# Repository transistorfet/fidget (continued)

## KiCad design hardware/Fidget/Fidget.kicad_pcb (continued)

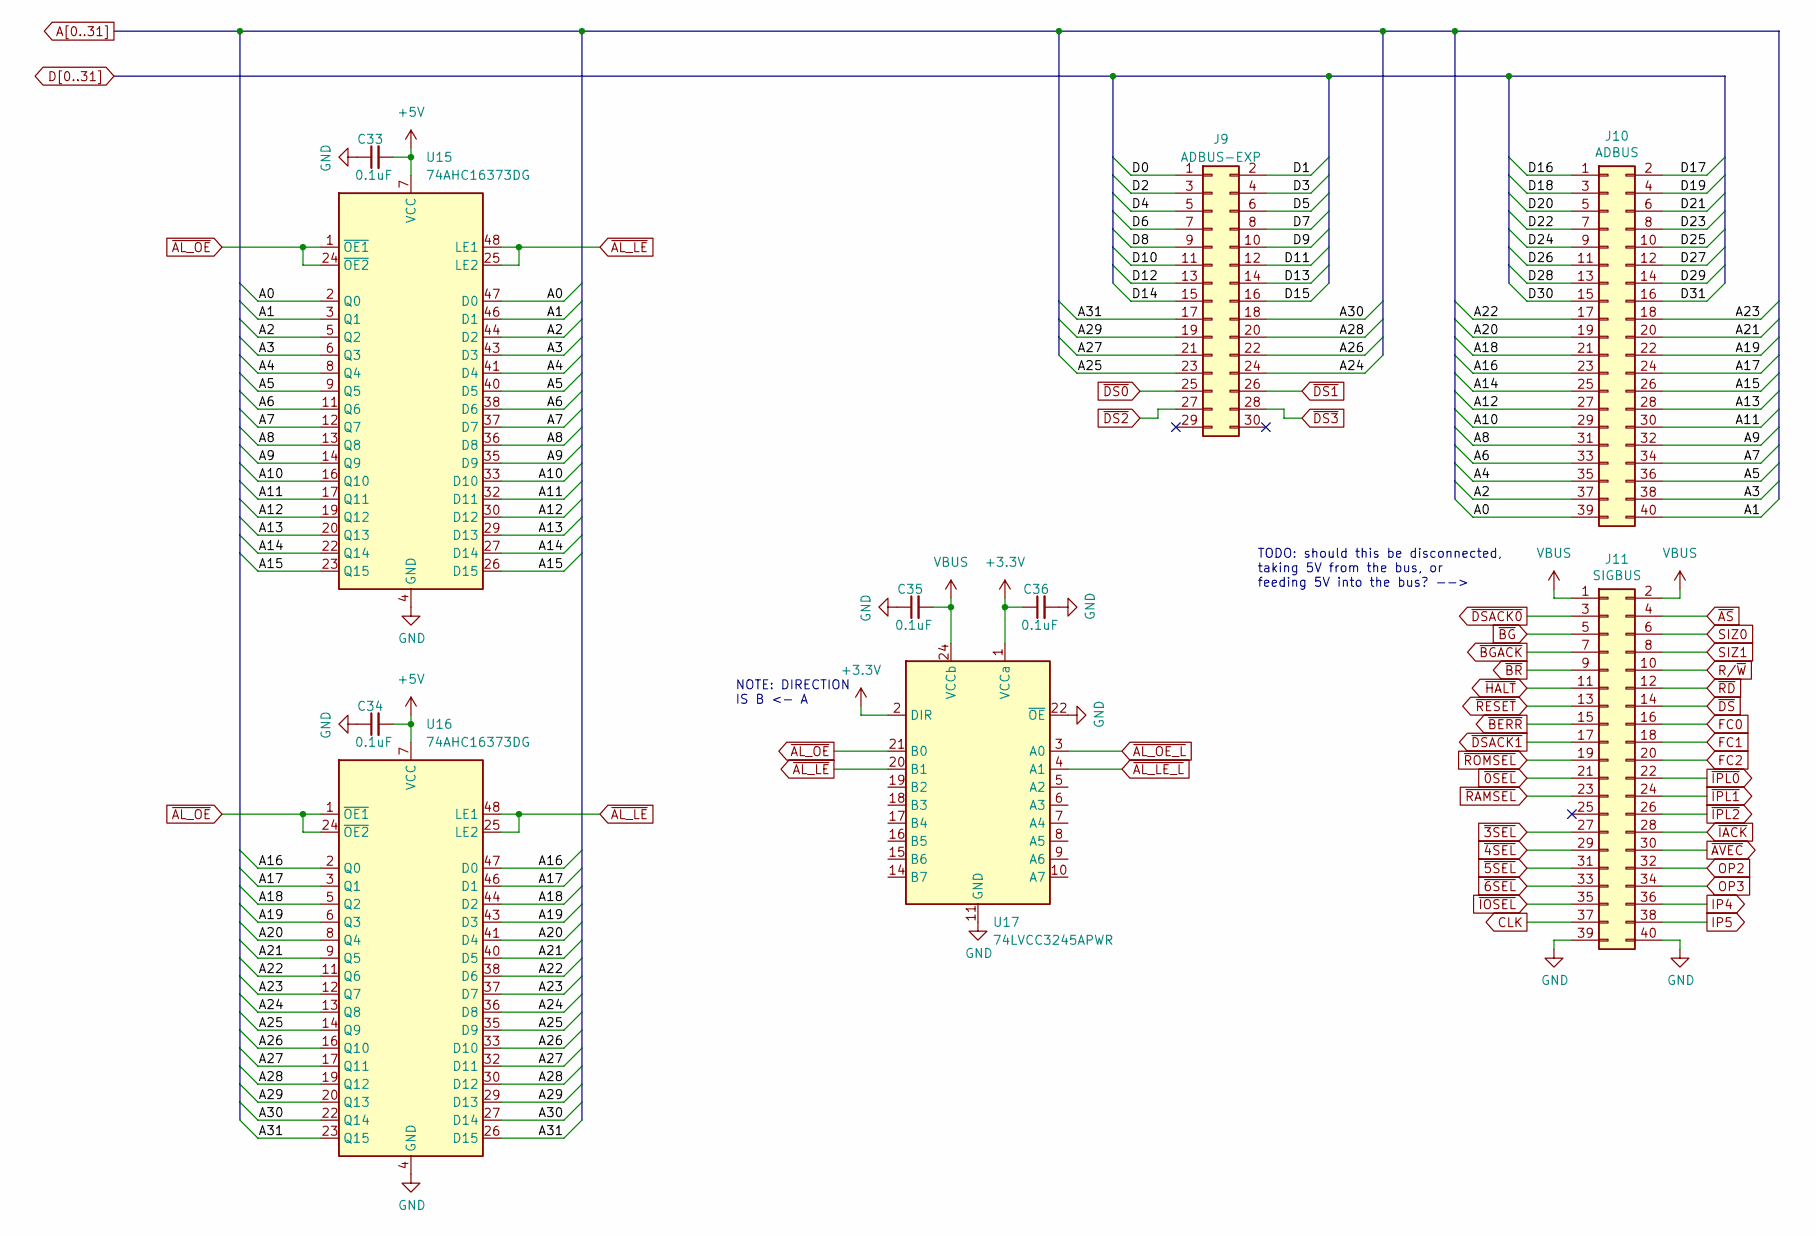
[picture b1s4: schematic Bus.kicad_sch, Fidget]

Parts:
C33, C34, C35, C36: 0.1uF; C_0805_2012Metric_Pad1.18x1.45mm_HandSolder
J9: ADBUS-EXP; PinHeader_2x15_P2.54mm_Vertical
J10: ADBUS; PinHeader_2x20_P2.54mm_Vertical
J11: SIGBUS; PinHeader_2x20_P2.54mm_Vertical
U15, U16: 74AHC16373DG; TSSOP-48_6.1x12.5mm_P0.5mm
U17: 74LVCC3245APWR; TSSOP-24_4.4x7.8mm_P0.65mm

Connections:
+3.3V: C36.1, U17.1 (VCCa), U17.2 (DIR); also elsewhere on the board
+5V: C33.2, C34.2, U15.7 (VCC), U15.18 (VCC), U15.31 (VCC), U15.42 (VCC), U16.7 (VCC), U16.18 (VCC), U16.31 (VCC), U16.42 (VCC); also elsewhere on the board
A0: J10.39, U15.2 (Q0), U15.47 (D0); also elsewhere on the board
A1: J10.40, U15.3 (Q1), U15.46 (D1); also elsewhere on the board
A2: J10.37, U15.5 (Q2), U15.44 (D2); also elsewhere on the board
A3: J10.38, U15.6 (Q3), U15.43 (D3); also elsewhere on the board
A4: J10.35, U15.8 (Q4), U15.41 (D4); also elsewhere on the board
A5: J10.36, U15.9 (Q5), U15.40 (D5); also elsewhere on the board
A6: J10.33, U15.11 (Q6), U15.38 (D6); also elsewhere on the board
A7: J10.34, U15.12 (Q7), U15.37 (D7); also elsewhere on the board
A8: J10.31, U15.13 (Q8), U15.36 (D8); also elsewhere on the board
A9: J10.32, U15.14 (Q9), U15.35 (D9); also elsewhere on the board
A10: J10.29, U15.16 (Q10), U15.33 (D10); also elsewhere on the board
A11: J10.30, U15.17 (Q11), U15.32 (D11); also elsewhere on the board
A12: J10.27, U15.19 (Q12), U15.30 (D12); also elsewhere on the board
A13: J10.28, U15.20 (Q13), U15.29 (D13); also elsewhere on the board
A14: J10.25, U15.22 (Q14), U15.27 (D14); also elsewhere on the board
A15: J10.26, U15.23 (Q15), U15.26 (D15); also elsewhere on the board
A16: J10.23, U16.2 (Q0), U16.47 (D0); also elsewhere on the board
A17: J10.24, U16.3 (Q1), U16.46 (D1); also elsewhere on the board
A18: J10.21, U16.5 (Q2), U16.44 (D2); also elsewhere on the board
A19: J10.22, U16.6 (Q3), U16.43 (D3); also elsewhere on the board
A20: J10.19, U16.8 (Q4), U16.41 (D4); also elsewhere on the board
A21: J10.20, U16.9 (Q5), U16.40 (D5); also elsewhere on the board
A22: J10.17, U16.11 (Q6), U16.38 (D6); also elsewhere on the board
A23: J10.18, U16.12 (Q7), U16.37 (D7); also elsewhere on the board
A24: J9.24, U16.13 (Q8), U16.36 (D8); also elsewhere on the board
A25: J9.23, U16.14 (Q9), U16.35 (D9); also elsewhere on the board
A26: J9.22, U16.16 (Q10), U16.33 (D10); also elsewhere on the board
A27: J9.21, U16.17 (Q11), U16.32 (D11); also elsewhere on the board
A28: J9.20, U16.19 (Q12), U16.30 (D12); also elsewhere on the board
A29: J9.19, U16.20 (Q13), U16.29 (D13); also elsewhere on the board
A30: J9.18, U16.22 (Q14), U16.27 (D14); also elsewhere on the board
A31: J9.17, U16.23 (Q15), U16.26 (D15); also elsewhere on the board
CLK: J11.37; also elsewhere on the board
D0: J9.1; also elsewhere on the board
D1: J9.2; also elsewhere on the board
D2: J9.3; also elsewhere on the board
D3: J9.4; also elsewhere on the board
D4: J9.5; also elsewhere on the board
D5: J9.6; also elsewhere on the board
D6: J9.7; also elsewhere on the board
D7: J9.8; also elsewhere on the board
D8: J9.9; also elsewhere on the board
D9: J9.10; also elsewhere on the board
D10: J9.11; also elsewhere on the board
D11: J9.12; also elsewhere on the board
D12: J9.13; also elsewhere on the board
D13: J9.14; also elsewhere on the board
D14: J9.15; also elsewhere on the board
D15: J9.16; also elsewhere on the board
D16: J10.1; also elsewhere on the board
D17: J10.2; also elsewhere on the board
D18: J10.3; also elsewhere on the board
D19: J10.4; also elsewhere on the board
D20: J10.5; also elsewhere on the board
D21: J10.6; also elsewhere on the board
D22: J10.7; also elsewhere on the board
D23: J10.8; also elsewhere on the board
D24: J10.9; also elsewhere on the board
D25: J10.10; also elsewhere on the board
D26: J10.11; also elsewhere on the board
D27: J10.12; also elsewhere on the board
D28: J10.13; also elsewhere on the board
D29: J10.14; also elsewhere on the board
D30: J10.15; also elsewhere on the board
D31: J10.16; also elsewhere on the board
FC0: J11.16; also elsewhere on the board
FC1: J11.18; also elsewhere on the board
FC2: J11.20; also elsewhere on the board
GND: C33.1, C34.1, C35.1, C36.2, J11.39, J11.40, U15.4 (GND), U15.10 (GND), U15.15 (GND), U15.21 (GND), U15.28 (GND), U15.34 (GND), U15.39 (GND), U15.45 (GND), U16.4 (GND), U16.10 (GND), U16.15 (GND), U16.21 (GND), U16.28 (GND), U16.34 (GND), U16.39 (GND), U16.45 (GND), U17.11 (GND), U17.12 (GND), U17.13 (GND), U17.22 (~OE); also elsewhere on the board
IP4: J11.36
IP5: J11.38
OP2: J11.32
OP3: J11.34
R/~W: J11.10; also elsewhere on the board
SIZ0: J11.6; also elsewhere on the board
SIZ1: J11.8; also elsewhere on the board
VBUS: C35.2, J11.1, J11.2, U17.24 (VCCb); also elsewhere on the board
~0SEL: J11.21
~3SEL: J11.27
~4SEL: J11.29
~5SEL: J11.31
~6SEL: J11.33
~AL_LE_L: U17.4 (A1); also elsewhere on the board
~AL_LE: U15.25 (LE2), U15.48 (LE1), U16.25 (LE2), U16.48 (LE1), U17.20 (B1)
~AL_OE_L: U17.3 (A0); also elsewhere on the board
~AL_OE: U15.1 (~OE1), U15.24 (~OE2), U16.1 (~OE1), U16.24 (~OE2), U17.21 (B0)
~AS: J11.4; also elsewhere on the board
~AVEC: J11.30; also elsewhere on the board
~BERR: J11.15; also elsewhere on the board
~BGACK: J11.7; also elsewhere on the board
~BG: J11.5; also elsewhere on the board
~BR: J11.9; also elsewhere on the board
~DS0: J9.25
~DS1: J9.26
~DS2: J9.27
~DS3: J9.28
~DSACK0: J11.3; also elsewhere on the board
~DSACK1: J11.17; also elsewhere on the board
~DS: J11.14; also elsewhere on the board
~HALT: J11.11; also elsewhere on the board
~IACK: J11.28; also elsewhere on the board
~IOSEL: J11.35
~IPL0: J11.22; also elsewhere on the board
~IPL1: J11.24; also elsewhere on the board
~IPL2: J11.26; also elsewhere on the board
~RAMSEL: J11.23
~RD: J11.12
~RESET: J11.13; also elsewhere on the board
~ROMSEL: J11.19

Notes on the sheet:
NOTE: DIRECTION IS B <- A
TODO: should this be disconnected, taking 5V from the bus, or feeding 5V into the bus? -->

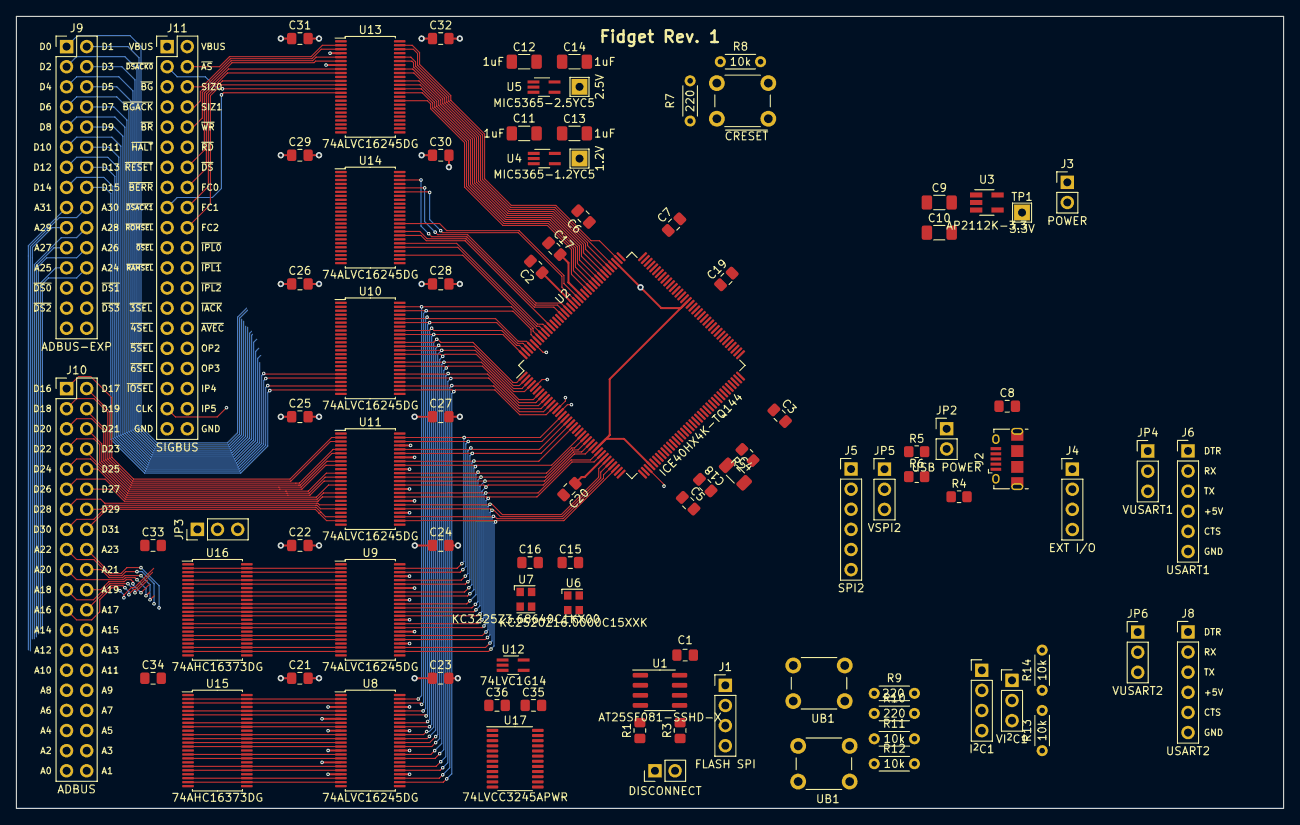
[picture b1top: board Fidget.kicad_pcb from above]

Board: 4 copper layers, 160.0 x 100.0 mm, 91 parts (0 on the bottom side), 204 nets.

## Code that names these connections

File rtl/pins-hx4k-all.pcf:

#
# FPGA:		Lattice iCE40 HX4K
# Package:	TQ-144
#
set_io -nowarn pin_ad[6]		1	# IOL_2A
set_io -nowarn pin_ad[7]		2       # IOL_2B
set_io -nowarn pin_ad[8]		3       # IOL_3A
set_io -nowarn pin_ad[9]		4       # IOL_3B
set_io -nowarn pin_ad[10]		7       # IOL_4A
set_io -nowarn pin_ad[11]		8       # IOL_4B
set_io -nowarn pin_ad[12]		9       # IOL_5A
set_io -nowarn pin_ad[13]		10      # IOL_5B
set_io -nowarn pin_ad[14]		11      # IOL_8A
set_io -nowarn pin_ad[15]		12      # IOL_8B
set_io -nowarn pin_ad[16]		15      # IOL_10A
set_io -nowarn pin_ad[17]		16      # IOL_10B
set_io -nowarn pin_ad[18]		17      # IOL_12A
set_io -nowarn pin_ad[19]		18      # IOL_12B
set_io -nowarn pin_ad[20]		19      # IOL_13A
set_io -nowarn pin_halt_in		20      # IOL_13B_GBIN7
set_io -nowarn pin_iack			21      # IOL_14A_GBIN6
set_io -nowarn pin_ad[21]		22      # IOL_14B
set_io -nowarn pin_ad[22]      		23      # IOL_17A
set_io -nowarn pin_ad[23]      		24      # IOL_17B
set_io -nowarn pin_ad[24]		25      # IOL_18A
set_io -nowarn pin_ad[25]		26      # IOL_18B
set_io -nowarn pin_ad[26]		28      # IOL_23A
set_io -nowarn pin_ad[27]		29      # IOL_23B
set_io -nowarn pin_ad[28]      		31      # IOL_24A
set_io -nowarn pin_ad[29]      		32      # IOL_24B
set_io -nowarn pin_ad[30]		33      # IOL_25A
set_io -nowarn pin_ad[31]		34      # IOL_25B
set_io -nowarn pin_avec			37      # IOB_56
set_io -nowarn pin_ctrl_oe     		38      # IOB_57
set_io -nowarn pin_alt_ctrl_oe 		39      # IOB_61
set_io -nowarn pin_alt_ctrl_dir1	41      # IOB_63
set_io -nowarn pin_alt_ctrl_dir2	42      # IOB_64
set_io -nowarn pin_data_dir		43      # IOB_71
set_io -nowarn pin_data_oe		44      # IOB_72
set_io -nowarn pin_send_receive		45      # IOB_73
set_io -nowarn pin_clk_16M		47      # IOB_79
set_io -nowarn pin_clk_3_6864M		48      # IOB_80
set_io -nowarn pin_addr_oe		49      # IOB_81_GBIN5
set_io -nowarn pin_al_oe		52      # IOB_82_GBIN4
set_io -nowarn pin_al_le		55      # IOB_91
set_io -nowarn pin_ul1			56      # IOB_94
set_io -nowarn pin_ul2			60      # IOB_95
set_io -nowarn pin_ul3			61      # IOB_96
set_io -nowarn pin_ul4			62      # IOB_102
set_io -nowarn pin_ub1			63      # IOB_103_CBSEL0
set_io -nowarn pin_ub2			64      # IOB_104_CBSEL1
set_io -nowarn pin_sdo			67      # IOB_105_SDO
set_io -nowarn pin_sdi			68      # IOB_106_SDI
set_io -nowarn pin_sck			70      # IOB_107_SCK
set_io -nowarn pin_scs			71      # IOB_108_SS
set_io -nowarn pin_sf_wp		73      # IOR_109
set_io -nowarn pin_sf_hold		74      # IOR_110
set_io -nowarn pin_sdo2			75      # IOR_111
set_io -nowarn pin_sdi2			76      # IOR_112
set_io -nowarn pin_sck2			78      # IOR_114
set_io -nowarn pin_scs2			79      # IOR_115
set_io -nowarn pin_sck1			80      # IOR_116
set_io -nowarn pin_sda1			81      # IOR_117
set_io -nowarn pin_usb_dn		82      # IOR_118
set_io -nowarn pin_usb_dp		83      # IOR_119
set_io -nowarn pin_usb_pullup		84      # IOR_120
set_io -nowarn pin_usart1_tx		85      # IOR_128
set_io -nowarn pin_usart1_rx		87      # IOR_136
set_io -nowarn pin_usart1_cts		88      # IOR_137, DTR on Rev1 (Input into FPGA)
set_io -nowarn pin_usart1_rts		90      # IOR_138, CTS on Rev1 (Output from FPGA)
set_io -nowarn pin_usart2_tx		91      # IOR_139
set_io -nowarn pin_usart2_rx		93      # IOR_140_GBIN3
set_io -nowarn pin_usart2_cts		94      # IOR_141_GBIN2, DTR on Rev1 (Input into FPGA)
set_io -nowarn pin_usart2_rts		95      # IOR_144, CTS on Rev1 (Output from FPGA)
set_io -nowarn pin_ext_1		96      # IOR_146
set_io -nowarn pin_ext_2		97      # IOR_147
set_io -nowarn pin_ext_3		98      # IOR_148
set_io -nowarn pin_ext_4		99      # IOR_152
set_io -nowarn pin_ext_5		101     # IOR_160
set_io -nowarn pin_ext_6		102     # IOR_161
set_io -nowarn pin_ext_7     		104     # IOR_164
set_io -nowarn pin_ext_8     		105     # IOR_165
set_io -nowarn pin_ext_9     		106     # IOR_166
set_io -nowarn pin_ext_10     		107     # IOR_167
set_io -nowarn pin_as			110     # IOT_168
set_io -nowarn pin_siz0			112     # IOT_169
set_io -nowarn pin_siz1			113     # IOT_170
set_io -nowarn pin_rw			114     # IOT_171
set_io -nowarn pin_ds			115     # IOT_172
set_io -nowarn pin_fc0			116     # IOT_173
set_io -nowarn pin_fc1			117     # IOT_174
set_io -nowarn pin_fc2			118     # IOT_177
set_io -nowarn pin_dsack0		119     # IOT_178
set_io -nowarn pin_dsack1		120     # IOT_179
set_io -nowarn pin_berr			121     # IOT_181
set_io -nowarn pin_halt_out		122     # IOT_190
set_io -nowarn pin_reset_out		124     # IOT_191
set_io -nowarn pin_bg			125     # IOT_192
set_io -nowarn pin_clk			128     # IOT_197_GBIN1
set_io -nowarn pin_reset_in		129     # IOT_198_GBIN0
set_io -nowarn pin_bgack		130     # IOT_206
set_io -nowarn pin_br			134     # IOT_212
set_io -nowarn pin_ipl0			135     # IOT_213
set_io -nowarn pin_ipl1			136     # IOT_214
set_io -nowarn pin_ipl2			137     # IOT_215
set_io -nowarn pin_ad[0]		138     # IOT_216
set_io -nowarn pin_ad[1]		139     # IOT_217
set_io -nowarn pin_ad[2]		141     # IOT_219
set_io -nowarn pin_ad[3]		142     # IOT_220
set_io -nowarn pin_ad[4]		143     # IOT_221
set_io -nowarn pin_ad[5]		144     # IOT_222

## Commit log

2023-01-08 Updated todo
2023-01-15 Added level shifting and some I/O assignments
2023-01-15 Added oscillators
2023-01-15 Added WIP schematic
2023-01-15 Assigned bus control signals to level shifters
2023-01-15 Added address latches
2023-01-16 Progress on sorting out the transceiver controls
2023-01-19 Added test of verilog to control the I/O pins bidirectionally
2023-01-19 Modified rtl to test spliting the addr/data bus that can run on tinyfpga
2023-01-20 Validated 2-bit bidirectional bus on TinyFPGA
2023-01-21 Added jumper to select bus voltage
2023-01-21 Added tinyfpga bootloader submodule
2023-01-22 Reorganized RTL into libraries
2023-01-22 Added testbenches for usart modules
2023-01-23 Filled in more details in schematic
2023-01-24 Got simple RTL experiment of USART<->Bus in TinyFPGA
2023-02-06 Minor updates, and start of PCB layout
2023-02-12 More PCB layout and fixes and reassigments to the schematics
2023-02-24 Almost done Rev1 board design
2023-02-25 Finished all connections in Rev1
2023-02-28 Changed crystal footprint and minor cleanup of Rev1 PCB
2023-03-05 Sent Rev.1 to production
2023-03-05 Added default hx4k pins
2023-04-03 The board is almost built, but tinyprog won't program it
    I seem to be missing meta data in the SPI flash
2023-04-08 Switched to a fork of TinyFPGA with Fidget board added
2023-04-08 Board is working with the bootloader and blinking led demo
2023-04-08 Added images of revision 1
2023-04-08 Updated readme again
2023-06-19 Added USART rtl that works in sim but isn't quite synthesizable
2023-06-22 Got the USART working at 57600 baud
    It just echos the input to the output, but it works. It just won't
    work at 115200 because as written, it can't have a clock divider less
    than 32
2023-06-24 Got 115,200 baud working by using the 16 MHz clock for comms
    I also changed the counters to count separately, and made them only
    last one comm clock period, since it doesn't need to be a 50% duty
    cycle, and that means there's no need to find the midpoint.
2023-06-25 Added USART FIFO and the start of a serial bus debugger
2023-07-01 Added computie bus snooper for bus debugger
2023-07-03 Moved serial clocks into respective impls
2023-07-09 Fixed many issues with the computie bus snooper, but dump is not quite working
    I had to leave a hack in-place where the computie bus snooper needs to convert
    the 32 bit number into a list of 4 bit numbers, which seems to either require
    SystemVerilog or manually unpacking the list, which I did, but which is not
    truely parametric according to BITWIDTH.
    It seems to record the correct data, but there's a problem with the passing of
    data to the usart transmitter, which doesn't properly wait for each character
2023-07-10 Modified usart tx to use state machine and added common makefile
    It prints the dump sort of correctly, but it prints double characters
    sometimes. This seems to be because the start_transmitting bit is
    always set, but trying to change that makes it send characters without
    waiting for them to be transmitted. I don't yet know the right
    pattern to be using here to make the interconnected modules work
2023-07-15 Added a serial echo config and started adding a computie bus receiver module
    There's still lots of bugs with the snooper, and the serial tx/rx
2023-07-23 Added RTS to usart rx (but not CTS)
2023-07-23 Added first attempt at an asynchronous fifo
2023-07-30 Added async fifo to usart echo and simplified usart tx/rx
    The usart tx/rx now are single clock and must be interfaced to the
    clock that is exposed, or else there will be timing errors. The
    fifo provides the clock crossing.
    It works except for a duplicate character on the first character
    transmitted after a lull
2023-07-30 Fixed dual port memory using ram tile
2023-08-03 Dump output of the bus snooper is working, but recording is not
    It now prints a header and footer, which is a single line feed, and
    the button starts the dump which proceeds until the end, but it will
    still print multiple dumps if the button is held.
    Recording doesn't work properly and using it causes the output to
    glitch, which makes me think it's continuously recording
2023-08-06 Broke up the snooper into 3 modules
2023-08-06 Modified to use an async fifo between snooper and dumper
    I also had to replace the generator in the memory module because it
    wasn't synthenizing properly, and I don't know why
    The interface to the ram wasn't working, which is why I replaced it
    with a fifo. The timing was off, but I know the fifo interface to
    ram works. Using the valid/ready signals for the dumper was great
    but the snooper, it isn't the best because the snooper can't wait
2023-08-06 Minor fixes and added dumper testbench
2023-08-07 Added computie-kicad-library and updated to KiCad 7.0
